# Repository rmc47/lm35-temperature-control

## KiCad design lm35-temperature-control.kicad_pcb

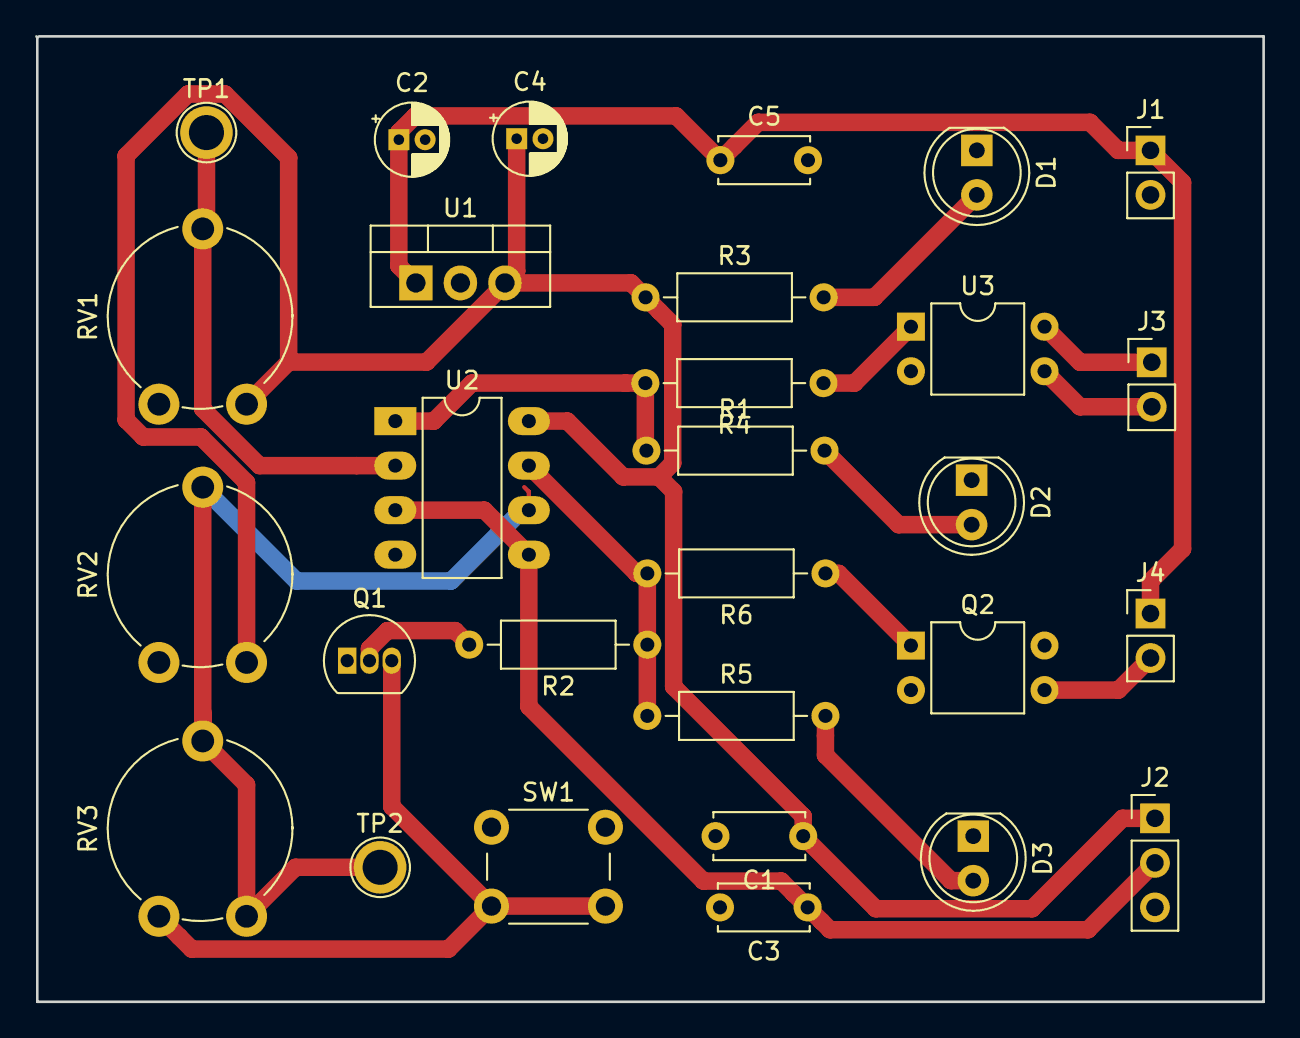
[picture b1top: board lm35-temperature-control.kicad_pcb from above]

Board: 2 copper layers, 70.0 x 55.1 mm, 29 parts (0 on the bottom side), 18 nets.

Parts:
C1, C3, C5: 100n; C_Disc_D5.0mm_W2.5mm_P5.00mm
C2, C4: 10u; CP_Radial_D4.0mm_P1.50mm
D1, D2, D3: LED; LED_D5.0mm
J1: 12VDC; PinHeader_1x02_P2.54mm_Vertical
J2: LM35DP; PinHeader_1x03_P2.54mm_Vertical
J3: Overtemp; PinHeader_1x02_P2.54mm_Vertical
J4: Fan; PinHeader_1x02_P2.54mm_Vertical
Q1: 2N3904; TO-92_Inline
Q2: IRLD014PBF; DIP-4_W7.62mm
R1, R3, R5: 1k; R_Axial_DIN0207_L6.3mm_D2.5mm_P10.16mm_Horizontal
R2, R6: 4k7; R_Axial_DIN0207_L6.3mm_D2.5mm_P10.16mm_Horizontal
R4: 390R; R_Axial_DIN0207_L6.3mm_D2.5mm_P10.16mm_Horizontal
RV1, RV2, RV3: 4k7; Potentiometer_Piher_PT-10-V10_Vertical
SW1: SW_Push; SW_PUSH_6mm
TP1, TP2: TestPoint; TestPoint_Plated_Hole_D2.0mm
U1: LM7805_TO220; TO-220-3_Vertical
U2: LM358; DIP-8_W7.62mm_LongPads
U3: TLP785; DIP-4_W7.62mm

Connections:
+5V: C1.1, C4.1, J2.1, R3.1, RV1.1, RV2.1, U1.3, U2.8
+12V: C2.1, C5.1, J1.1, J4.1, U1.1
GND: C1.2, C2.2, C3.2, C4.2, C5.2, D1.1, D2.1, D3.1, J1.2, J2.3, Q1.1, Q2.2, RV1.3, RV2.3, SW1.1, U1.2, U2.4, U3.2
unnamed: C3.1, J2.2, U2.3, U2.5
unnamed: D1.2, R3.2
unnamed: D2.2, R1.2
unnamed: D3.2, R5.2
unnamed: J3.1, U3.4
unnamed: J3.2, U3.3
unnamed: J4.2, Q2.3
unnamed: Q1.2, R2.2
unnamed: Q1.3, RV3.3, SW1.2
unnamed: Q2.1, R6.1
unnamed: R1.1, R4.2, U2.1
unnamed: R2.1, R5.1, R6.2, U2.7
unnamed: R4.1, U3.1
unnamed: RV1.2, TP1.1, U2.2
unnamed: RV2.2, RV3.1, RV3.2, TP2.1, U2.6
